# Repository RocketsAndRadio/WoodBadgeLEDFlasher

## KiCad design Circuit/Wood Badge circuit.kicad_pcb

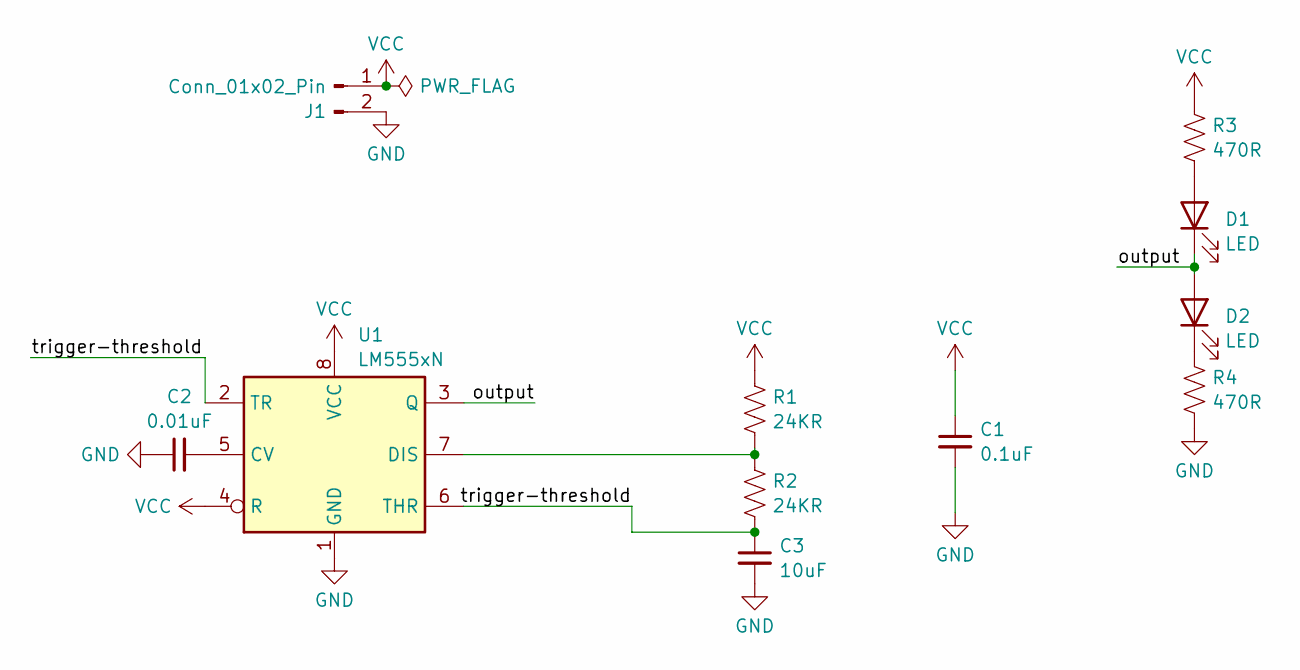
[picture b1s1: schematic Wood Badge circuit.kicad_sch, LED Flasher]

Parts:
C1: 0.1uF; CP_Radial_D5.0mm_P2.50mm
C2: 0.01uF; CP_Radial_D5.0mm_P2.50mm
C3: 10uF; CP_Radial_D5.0mm_P2.50mm
D1, D2: LED; LED_D5.0mm_Clear
J1: Conn_01x02_Pin; SolderWire-0.1sqmm_1x02_P3.6mm_D0.4mm_OD1mm
R1, R2: 24KR; R_Axial_DIN0411_L9.9mm_D3.6mm_P15.24mm_Horizontal
R3, R4: 470R; R_Axial_DIN0411_L9.9mm_D3.6mm_P15.24mm_Horizontal
U1: LM555xN; DIP-8_W7.62mm

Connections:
/output: D1.1 (K), D2.2 (A), U1.3 (Q)
/trigger-threshold: C3.1, R2.2, U1.2 (TR), U1.6 (THR)
GND: C1.2, C2.1, C3.2, J1.2, R4.2, U1.1 (GND)
unnamed: D1.2 (A), R3.2
unnamed: D2.1 (K), R4.1
unnamed: C2.2, U1.5 (CV)
unnamed: R1.2, R2.1, U1.7 (DIS)
VCC: C1.1, J1.1, R1.1, R3.1, U1.4 (R), U1.8 (VCC)

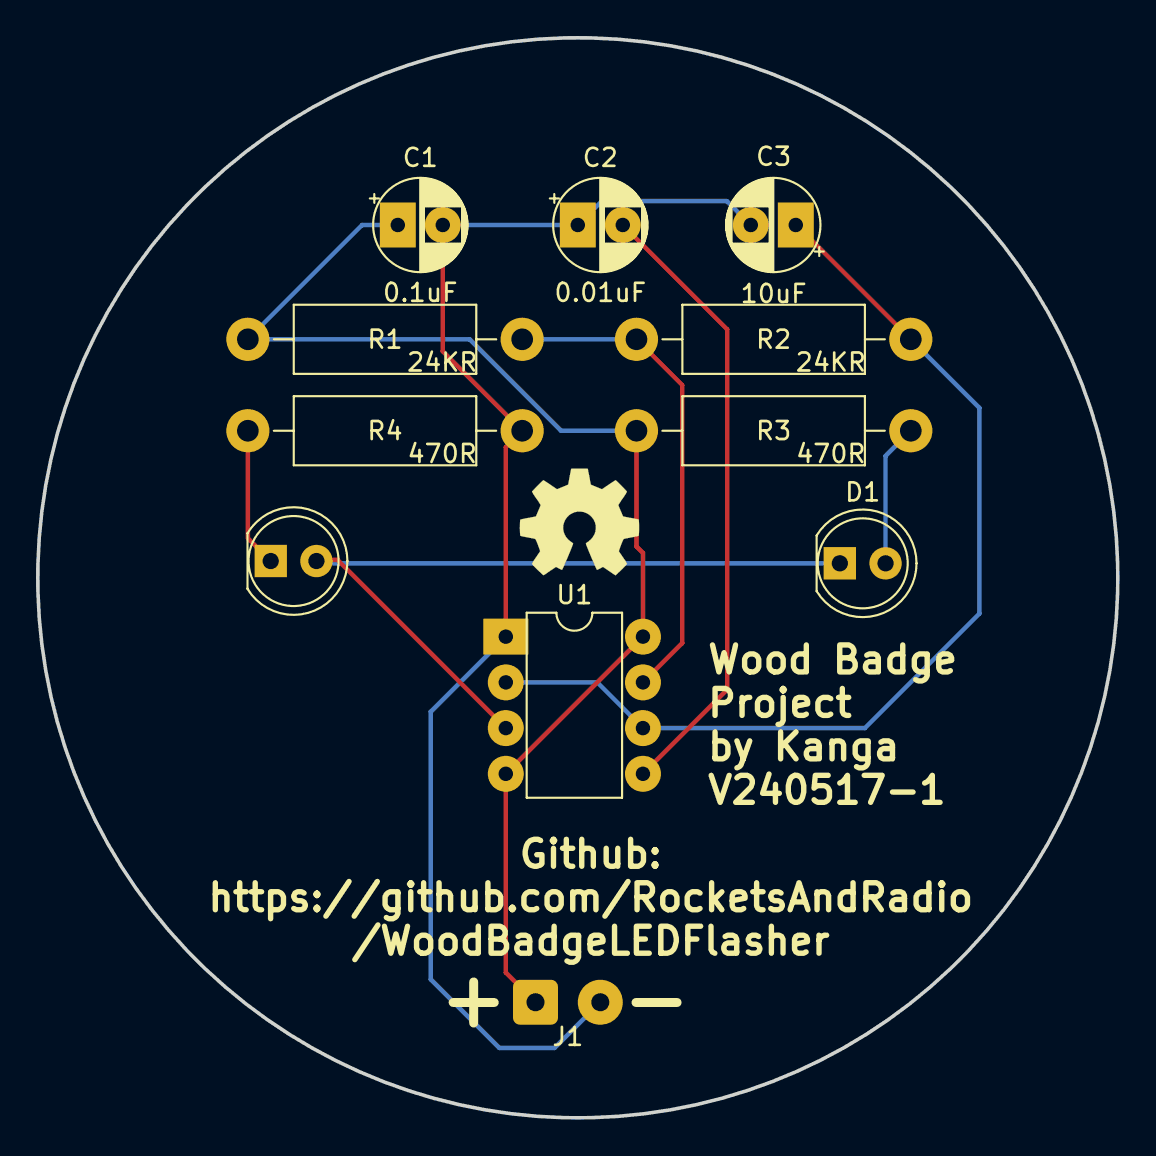
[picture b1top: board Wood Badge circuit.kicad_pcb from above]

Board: 2 copper layers, 60.0 x 60.0 mm, 11 parts (0 on the bottom side), 8 nets.

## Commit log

2024-03-23 Finished circuit. Submitted this desgin to PCBWay
2024-03-30 Conversion to Kicad 8.0
2024-04-23 Added C3 (below R1, R2 oops) Added values of components to reach a 2Hz frequency
2024-06-05 Amendments to reflect fixes for faults identified in the first time the circuit was put together, such as adding capacitor C3.
2024-09-06 Added first version of the Instructions
2024-10-18 Added images to Instructions.docx
2024-11-16 Added: + and - on the solar panel connection LED outline to show where the 'flat edge' needs to go
